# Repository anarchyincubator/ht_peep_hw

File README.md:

# ht_peep_hw
kicad for peep hw platform

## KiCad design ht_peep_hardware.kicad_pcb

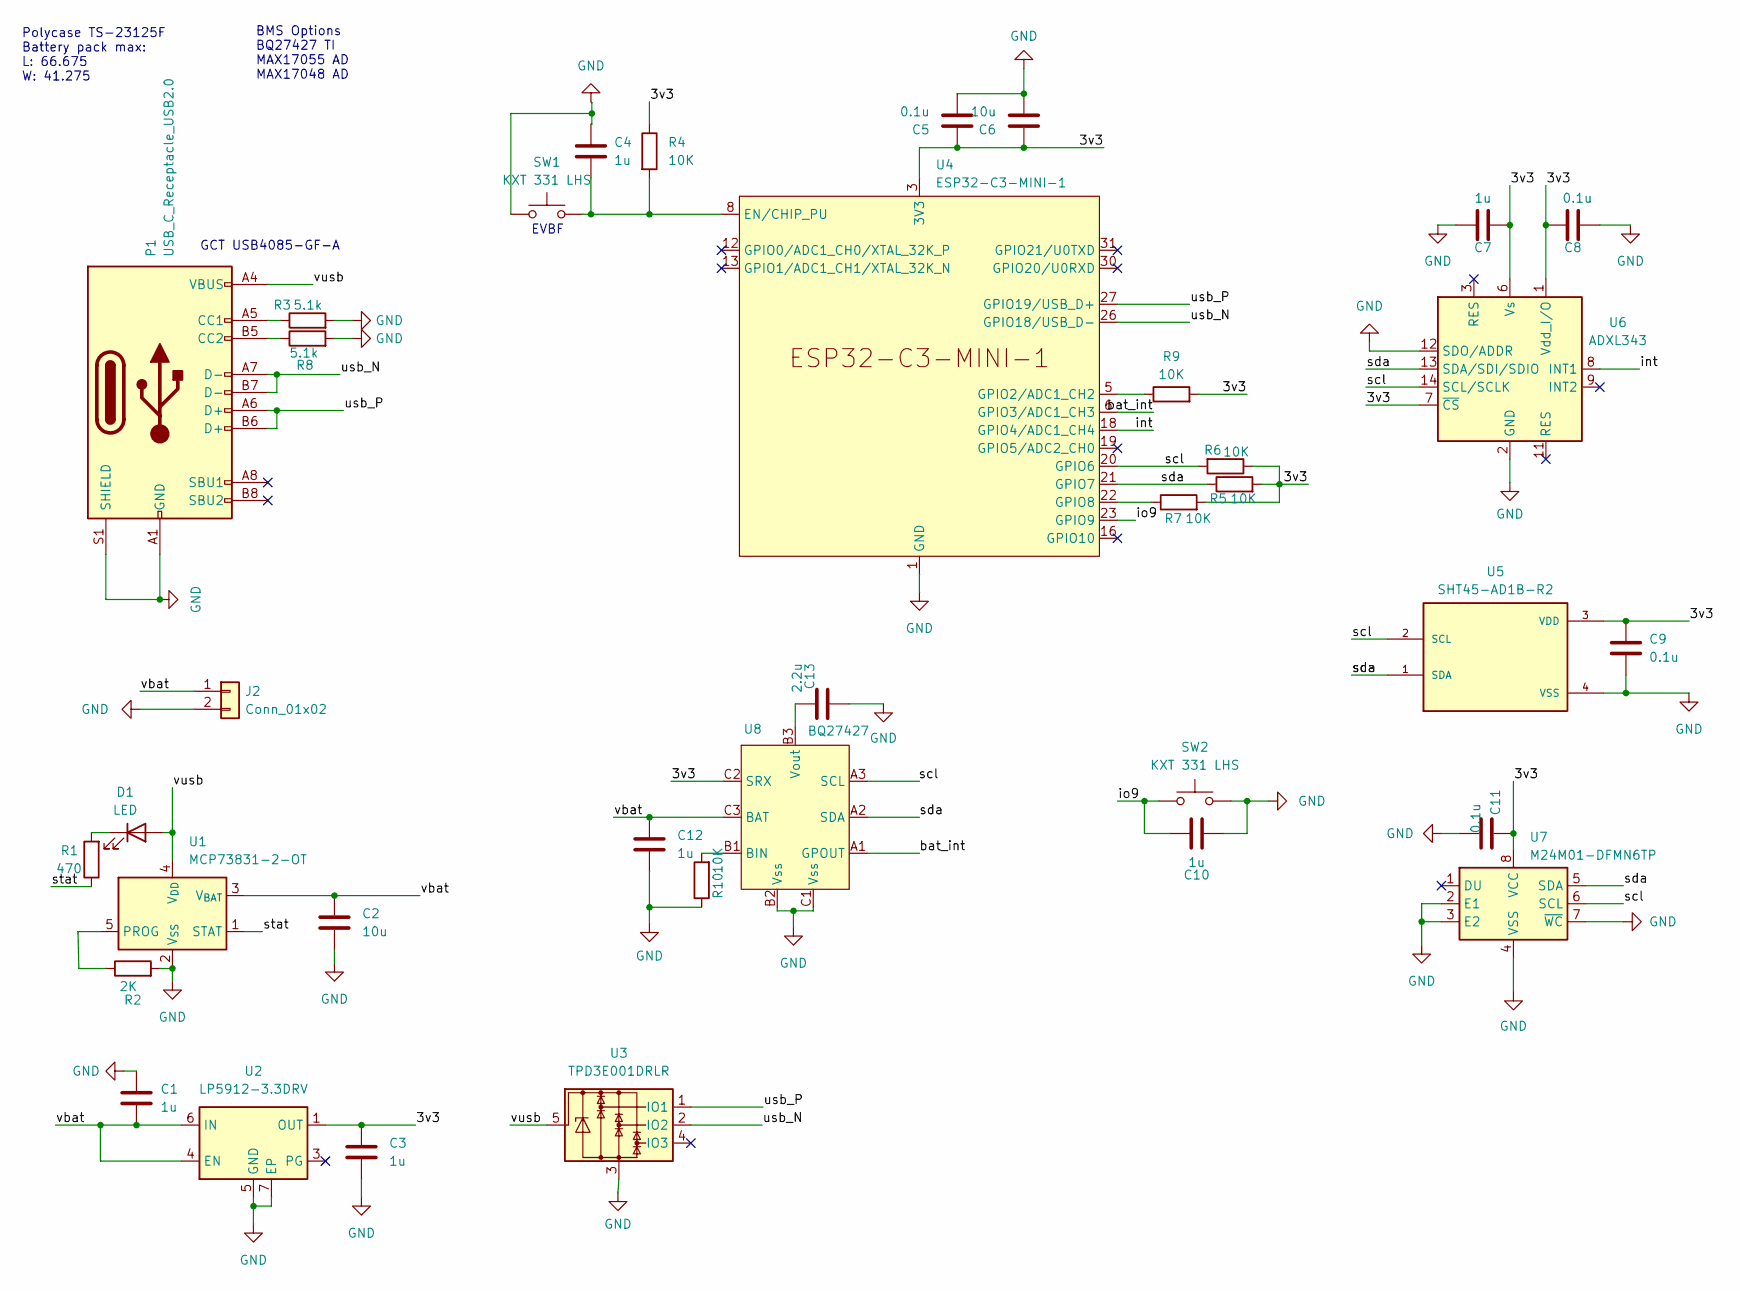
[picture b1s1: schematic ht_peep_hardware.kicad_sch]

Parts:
C1, C3, C4, C7, C10, C12: 1u; C_0402_1005Metric
C2, C6: 10u; C_0402_1005Metric
C5, C8, C9, C11: 0.1u; C_0402_1005Metric
C13: 2.2u; C_0402_1005Metric
D1: LED; LED_0402_1005Metric
J2: Conn_01x02; JST_ZE_S02B-ZESK-2D_1x02_P1.50mm_Horizontal
P1: USB_C_Receptacle_USB2.0; USB_C_Receptacle_GCT_USB4085
R1: 470; R_0402_1005Metric
R2: 2K; R_0402_1005Metric
R3, R8: 5.1k; R_0402_1005Metric
R4, R5, R6, R7, R9, R10: 10K; R_0402_1005Metric
SW1, SW2: KXT 331 LHS; SW_SPST_CK_KXT3
U1: MCP73831-2-OT; SOT-23-5
U2: LP5912-3.3DRV; WSON-6-1EP_2x2mm_P0.65mm_EP1x1.6mm_ThermalVias
U3: TPD3E001DRLR; SOT-553
U4: ESP32-C3-MINI-1
U5: SHT45-AD1B-R2; SHT4X
U6: ADXL343; LGA-14_3x5mm_P0.8mm_LayoutBorder1x6y
U7: M24M01-DFMN6TP; SOIC-8_3.9x4.9mm_P1.27mm
U8: BQ27427; Texas_DSBGA-9_1.4715x1.4715mm_Layout3x3_P0.5mm

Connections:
/3v3: C3.1, C5.1, C6.1, C7.1, C8.2, C9.1, C11.2, R4.1, R5.2, R6.1, R7.2, R9.2, U2.1 (OUT), U4.3 (3V3), U5.3 (VDD), U6.1 (Vdd_I/O), U6.6 (Vs), U6.7 (~CS), U7.8 (VCC), U8.C2 (SRX)
/bat_int: U4.6 (GPIO3/ADC1_CH3), U8.A1 (GPOUT)
/int: U4.18 (GPIO4/ADC1_CH4), U6.8 (INT1)
/io9: C10.2, SW2.1, U4.23 (GPIO9)
/scl: R6.2, U4.20 (GPIO6), U5.2 (SCL), U6.14 (SCL/SCLK), U7.6 (SCL), U8.A3 (SCL)
/sda: R5.1, U4.21 (GPIO7), U5.1 (SDA), U6.13 (SDA/SDI/SDIO), U7.5 (SDA), U8.A2 (SDA)
/stat: R1.1, U1.1 (STAT)
/usb_N: P1.A7 (D-), P1.B7 (D-), U3.2 (IO2), U4.26 (GPIO18/USB_D-)
/usb_P: P1.A6 (D+), P1.B6 (D+), U3.1 (IO1), U4.27 (GPIO19/USB_D+)
/vbat: C1.1, C2.1, C12.1, J2.1, U1.3 (V_{BAT}), U2.4 (EN), U2.6 (IN), U8.C3 (BAT)
/vusb: D1.2 (A), P1.A4 (VBUS), P1.A9 (VBUS), P1.B4 (VBUS), P1.B9 (VBUS), U1.4 (V_{DD}), U3.5
GND: C1.2, C2.2, C3.2, C4.1, C5.2, C6.2, C7.2, C8.1, C9.2, C10.1, C11.1, C12.2, C13.2, J2.2, P1.A1 (GND), P1.A12 (GND), P1.B1 (GND), P1.B12 (GND), P1.S1 (SHIELD), R2.2, R3.2, R8.2, R10.1, SW1.1, SW2.2, U1.2 (V_{SS}), U2.5 (GND), U2.7 (EP), U3.3, U4.1 (GND), U4.2 (GND), U4.11 (GND), U4.14 (GND), U4.36 (GND), U4.37 (GND), U4.38 (GND), U4.39 (GND), U4.40 (GND), U4.41 (GND), U4.42 (GND), U4.43 (GND), U4.44 (GND), U4.45 (GND), U4.46 (GND), U4.47 (GND), U4.48 (GND), U4.49 (GND), U4.50 (GND), U4.51 (GND), U4.52 (GND), U4.53 (GND), U5.4 (VSS), U6.2 (GND), U6.4 (GND), U6.5 (GND), U6.12 (SDO/ADDR), U7.2 (E1), U7.3 (E2), U7.4 (VSS), U7.7 (~WC), U8.B2 (Vss), U8.C1 (Vss)
unnamed: D1.1 (K), R1.2
unnamed: P1.A5 (CC1), R3.1
unnamed: P1.B5 (CC2), R8.1
unnamed: R2.1, U1.5 (PROG)
unnamed: C4.2, R4.2, SW1.2, U4.8 (EN/CHIP_PU)
unnamed: R9.1, U4.5 (GPIO2/ADC1_CH2)
unnamed: R7.1, U4.22 (GPIO8)
unnamed: R10.2, U8.B1 (BIN)
unnamed: C13.1, U8.B3 (Vout)

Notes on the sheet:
EVBF
BMS Options BQ27427 TI MAX17055 AD MAX17048 AD
Polycase TS-23125F Battery pack max: L: 66.675 W: 41.275
GCT USB4085-GF-A

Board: 2 copper layers, 36 parts (2 on the bottom side), 21 nets, no tracks yet.

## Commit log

2022-04-03 initial commit of peep hardware
2024-10-20 updated schematic w/ USB and C1 fix
